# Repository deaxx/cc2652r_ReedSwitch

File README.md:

<p><strong>CC2652R/RB ReedSwitch </strong></p>
<p>Box</p>
<p><a href="https://a.aliexpress.com/_9vHRin">https://a.aliexpress.com/_9vHRin </a></p>
<p>CR2032 holder</p>
<p><a href="https://a.aliexpress.com/_AqIH2X">https://a.aliexpress.com/_AqIH2X </a></p>
<p>https://a.aliexpress.com/_9hSXHd</p>

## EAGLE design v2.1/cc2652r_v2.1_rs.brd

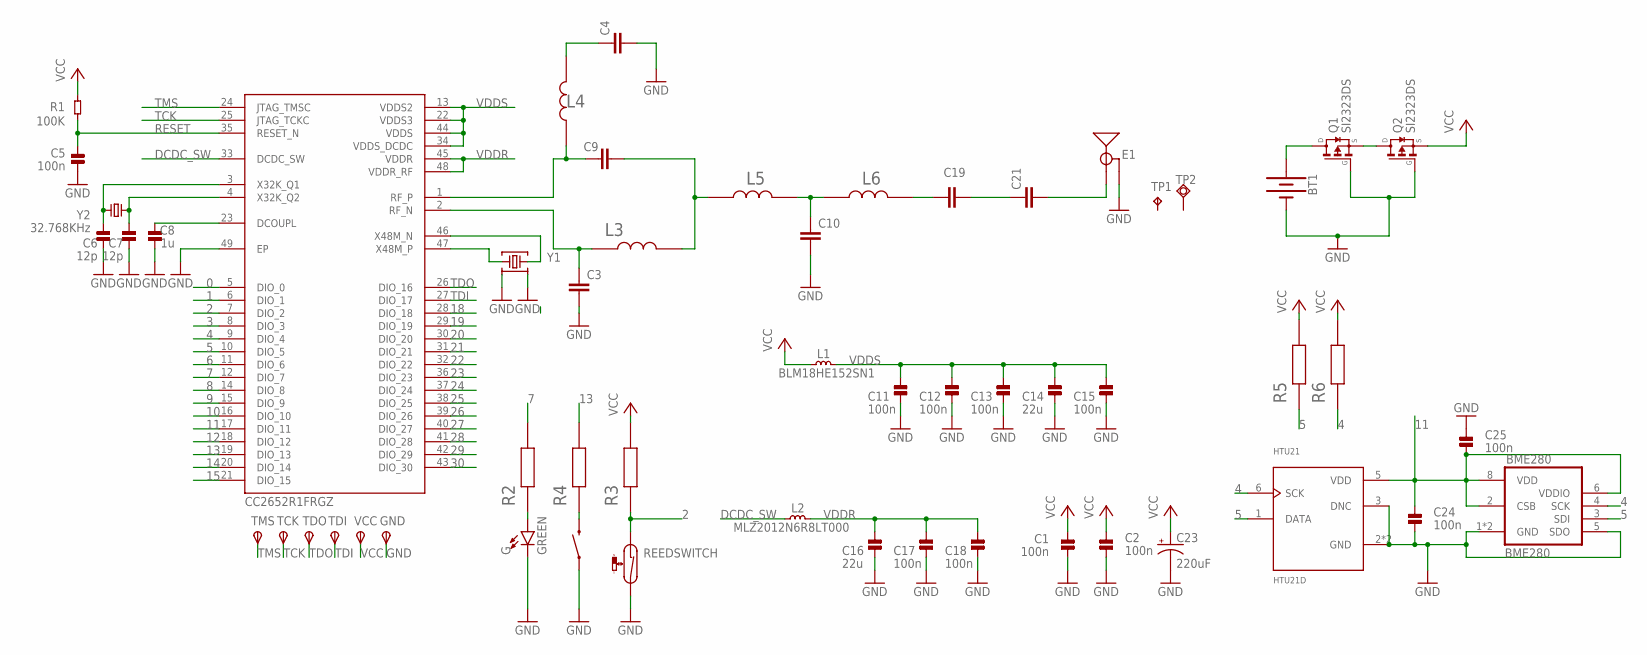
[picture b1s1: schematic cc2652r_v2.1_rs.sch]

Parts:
BME280: BME280
BT1: BATTERY-20MM_SMD; BATTCON_20MM
C1, C2, C5, C11, C12, C13, C15, C17, C18, C24, C25: 100n; _PKG_C_0402
C3: 1pf; CAPC1005X40N
C4, C19: 12pF; CAPC1005X40N
C6, C7: 12p; _PKG_C_0402
C8: 1u; _PKG_C_0402
C9, C10: 1pF; CAPC1005X40N
C14, C16: 22u; _PKG_C_0805
C21: 1.8pF; CAPC1005X40N
C23: 220uF; EIA3528
E1: ANTENNA-GROUNDEDTRACE-15.2MM; TRACE_ANTENNA_2.4GHZ_15.2MM
G: GREEN; LED-0603
GND: TPSTP11R; TP11R
HTU21: HTU21D; QFN100P300X300X100-7N
IC3: CC2652R1FRGZ; QFN50P700X700X100-49N
L1: BLM18HE152SN1; _PKG_L_0603
L2: MLZ2012N6R8LT000; _PKG_C_0805
L3, L4: 2.4nH; INDC1005X40N
L5, L6: 2nH; INDC1005X40N
Q1, Q2: SI2323DS; SOT23
R1: 100K; _PKG_C_0402
R2: 2.2k; RESC1005X40N
R3: 510k; RESC1005X40N
R4: 100Ohm; RESC1005X40N
R5, R6: 10k; RESC1005X40N
REEDSWITCH: REED-SWITCH-MK6-5-B; MK6-5
SW1: MOMENTARY-SWITCH-SPST-SMD-4.6X2.8MM; TACTILE_SWITCH_SMD_4.6X2.8MM
TCK: TPSTP11R; TP11R
TDI: TPSTP11R; TP11R
TDO: TPSTP11R; TP11R
TMS: TPSTP11R; TP11R
TP1: TPTP06SQ; TP05SQ
TP2: TPSQTP15SQ; TP15SQ
VCC: TPSTP11R; TP11R
Y1: Q22FA12800150; XTAL-4P-2016
Y2: 32.768KHz; XTAL-2P-3215

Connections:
0: IC3.5 (DIO_0)
1: IC3.6 (DIO_1)
2: IC3.7 (DIO_2), R3.1, REEDSWITCH.1
3: IC3.8 (DIO_3)
4: BME280.4 (SCK), HTU21.6 (SCK), IC3.9 (DIO_4), R6.1
5: BME280.3 (SDI), HTU21.1 (DATA), IC3.10 (DIO_5), R5.1
6: IC3.11 (DIO_6)
7: IC3.12 (DIO_7), R2.2
8: IC3.14 (DIO_8)
9: IC3.15 (DIO_9)
10: IC3.16 (DIO_10)
11: BME280.2 (CSB), BME280.6 (VDDIO), BME280.8 (VDD), C24.2, C25.1, HTU21.5 (VDD), IC3.17 (DIO_11)
12: IC3.18 (DIO_12)
13: IC3.19 (DIO_13), R4.2
14: IC3.20 (DIO_14)
15: IC3.21 (DIO_15)
18: IC3.28 (DIO_18)
19: IC3.29 (DIO_19)
20: IC3.30 (DIO_20)
21: IC3.31 (DIO_21)
22: IC3.32 (DIO_22)
23: IC3.36 (DIO_23)
24: IC3.37 (DIO_24)
25: IC3.38 (DIO_25)
26: IC3.39 (DIO_26)
27: IC3.40 (DIO_27)
28: IC3.41 (DIO_28)
29: IC3.42 (DIO_29)
30: IC3.43 (DIO_30)
DCDC_SW: IC3.33 (DCDC_SW), L2.1
DCOUPL: C8.2, IC3.23 (DCOUPL)
GND: BME280.1 (GND), BME280.5 (SDO), BME280.7 (GND), BT1.2 (-), C1.1, C2.1, C3.2, C4.2, C5.1, C6.1, C7.1, C8.1, C10.2, C11.2, C12.2, C13.2, C14.2, C15.2, C16.2, C17.2, C18.2, C23.C (-), C24.1, C25.2, E1.GND, G.C, GND.TP, HTU21.2 (GND), HTU21.3 (DNC), HTU21.PAD (GND), IC3.49 (EP), Q1.1 (G), Q2.1 (G), REEDSWITCH.2, SW1.1, SW1.2 (1), Y1.2, Y1.4
unnamed: C9.1, IC3.1 (RF_P), L4.1
unnamed: C3.1, IC3.2 (RF_N), L3.1
unnamed: C4.1, L4.2
unnamed: C9.2, L3.2, L5.1
unnamed: C19.1, L6.2
unnamed: R4.1, SW1.3 (2), SW1.4 (2)
unnamed: C19.2, C21.1
unnamed: BT1.1 (+), Q1.3 (D)
unnamed: C21.2, E1.ANT (SIGNAL)
unnamed: C10.1, L5.2, L6.1
unnamed: G.A, R2.1
unnamed: Q1.2 (S), Q2.3 (D)
RESET: C5.2, IC3.35 (RESET_N), R1.1
TCK: IC3.25 (JTAG_TCKC), TCK.TP
TDI: IC3.27 (DIO_17), TDI.TP
TDO: IC3.26 (DIO_16), TDO.TP
TMS: IC3.24 (JTAG_TMSC), TMS.TP
VCC: C1.2, C2.2, C23.A (+), L1.1, Q2.2 (S), R1.2, R3.2, R5.2, R6.2, VCC.TP
VDDR: C16.1, C17.1, C18.1, IC3.45 (VDDR), IC3.48 (VDDR_RF), L2.2
VDDS: C11.1, C12.1, C13.1, C14.1, C15.1, IC3.13 (VDDS2), IC3.22 (VDDS3), IC3.34 (VDDS_DCDC), IC3.44 (VDDS), L1.2
X32K_Q1: C6.2, IC3.3 (X32K_Q1), Y2.1
X32K_Q2: C7.2, IC3.4 (X32K_Q2), Y2.2
X48M_N: IC3.46 (X48M_N), Y1.3
X48M_P: IC3.47 (X48M_P), Y1.1

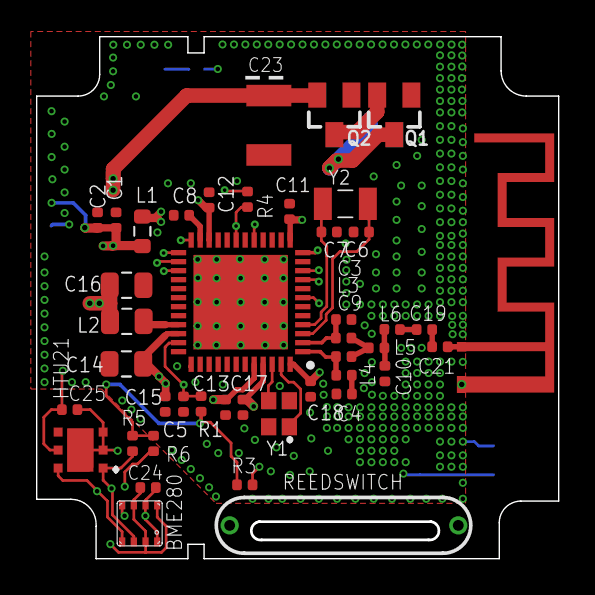
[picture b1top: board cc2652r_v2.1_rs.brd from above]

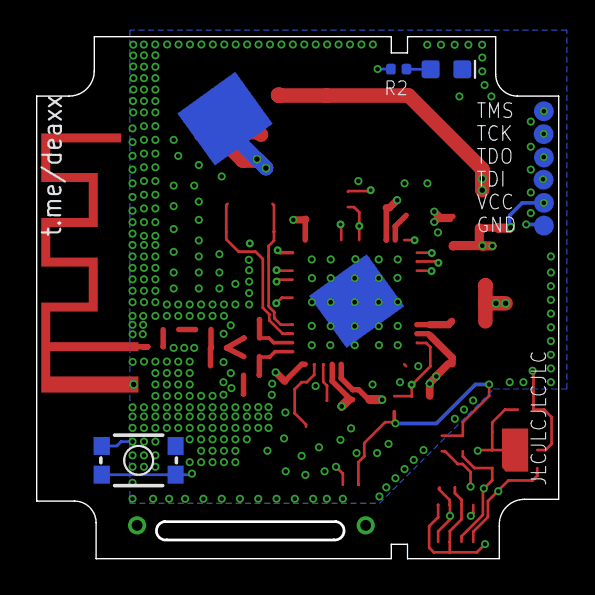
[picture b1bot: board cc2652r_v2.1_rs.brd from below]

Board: 4 copper layers, 29.0 x 29.0 mm, 55 parts (10 on the bottom side), 33 nets.

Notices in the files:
parts and their libraries:
SparkFun-LED: Licensing: Creative Commons ShareAlike 4.0 International - https://creativecommons.org/licenses/by-sa/4.0
